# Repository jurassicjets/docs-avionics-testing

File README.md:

# Jurassic Jets — Avionics Documentation

Bench-test notes, pinout discoveries, signal traces, and "how does this LRU actually work" writeups for the electromechanical and early-digital avionics that lived in 707s, 727s, 737-classics, 747-classics, DC-8s, DC-9s, L-1011s, and their kin.

This repo is the institutional knowledge base for what we learn at the bench. It's organized so a contributor — sim enthusiast or active commercial captain — can find the unit they care about, see what's known about it, and add what they've learned.

## Navigation

The repo splits content along two axes: how the *airframe* is configured, and what each *unit* is.

- **[avionics/](avionics/)** — Unit-level registry. One folder per LRU type, documenting pinouts, behavior, bench tests, quirks, datasheets — written once regardless of how many copies exist or how many airframes carry it.
- **[aircraft/](aircraft/)** — Per-airframe configuration. Each aircraft has cockpit map and `panels/<panel>/<module>/` — the module README is the leaf and lists each install slot, linking out to `avionics/`. Currently: [b747-300-ja8179](aircraft/b747-300-ja8179/README.md).
- **[systems/](systems/)** — Cross-cutting topics that span multiple instruments and airframes: ARINC 429, synchros, 28 VDC distribution, 400 Hz AC, etc. Also where generic test methods (sniffing a bus, exciting a synchro) live, alongside the protocol they apply to.
- **[templates/](templates/)** — Starter scaffolds. Copy-paste, then fill in.
- **[glossary.md](glossary.md)** — Acronyms, part-number conventions, and term-of-art definitions.

## Contributing

Read **[CONTRIBUTING.md](CONTRIBUTING.md)** before adding content. It covers naming conventions, the per-instrument file skeleton, image and large-file handling, and how to handle instruments that appear in multiple aircraft.

## Docs site

Rendered with [MkDocs Material](https://squidfunk.github.io/mkdocs-material/) and deployed to **[avionics-docs.jurassicjets.com](https://avionics-docs.jurassicjets.com/)** on every push to `main` via [GitHub Actions](https://github.com/jurassicjets/docs-avionics-testing/blob/main/.github/workflows/docs.yml). GitHub also renders the markdown directly in this repo, so you don't need any tooling to read or contribute.

### Building the site locally

MkDocs forbids `docs_dir` from being the parent of `mkdocs.yml`, but we want content to live at the repo root rather than under a `docs/` wrapper. The build uses a tiny staging step ([`scripts/stage_docs.sh`](scripts/stage_docs.sh)) that creates a `_site_src/` directory of symlinks pointing back to the real files. Edits to the source files are visible immediately because they're symlinks, so `mkdocs serve` works normally after one stage.

```bash
pip install -r requirements-docs.txt
./scripts/stage_docs.sh
mkdocs serve
```

Then open <http://localhost:8000>. Edits to existing files hot-reload; if you add a new top-level item (a new directory at the repo root), re-run `./scripts/stage_docs.sh`.

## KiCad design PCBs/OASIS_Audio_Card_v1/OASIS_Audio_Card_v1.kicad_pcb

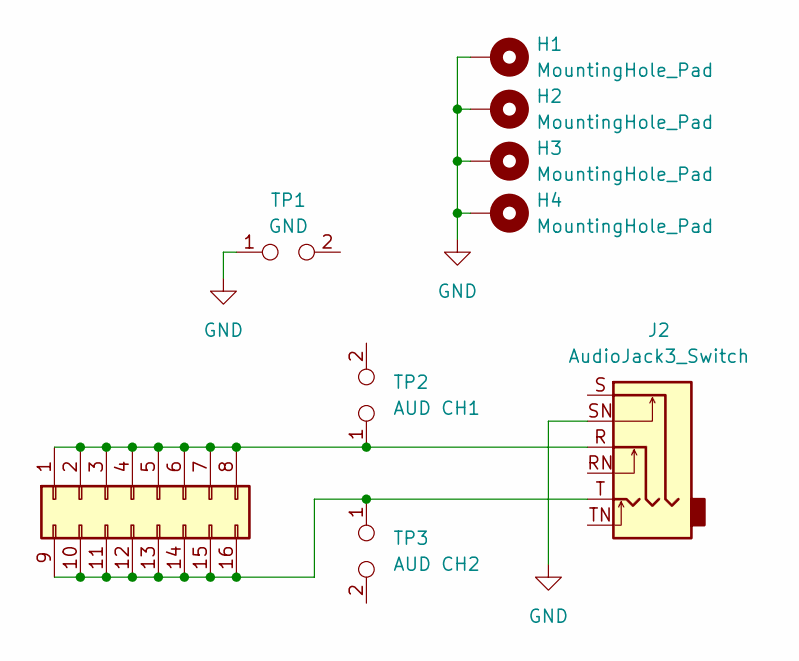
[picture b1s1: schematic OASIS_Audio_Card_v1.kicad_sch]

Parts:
H1, H2, H3, H4: MountingHole_Pad; MountingHole_3.2mm_M3_Pad
J1: Conn_02x08_Top_Bottom; 2x08_3.5mm_Phoenix_Connector_knockoff_convertible
J2: AudioJack3_Switch; TRS_2_Pole_THT
TP1: GND; PinHeader_1x02_P2.54mm_Vertical
TP2: AUD CH1; PinHeader_1x02_P2.54mm_Vertical
TP3: AUD CH2; PinHeader_1x02_P2.54mm_Vertical

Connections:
GND: H1.1, H2.1, H3.1, H4.1, J2.SN, TP1.1
unnamed: J1.1, J1.2, J1.3, J1.4, J1.5, J1.6, J1.7, J1.8, J2.R, TP2.1
unnamed: J1.9, J1.10, J1.11, J1.12, J1.13, J1.14, J1.15, J1.16, J2.T, TP3.1

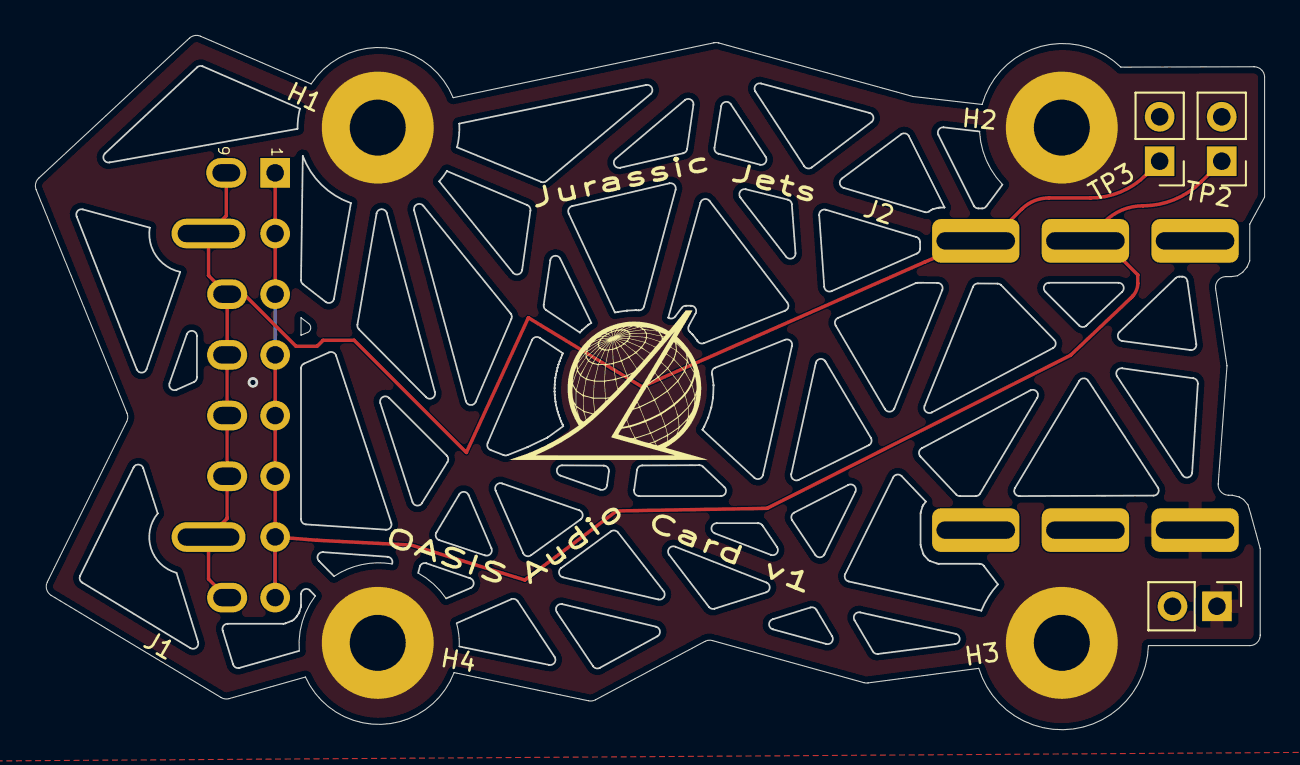
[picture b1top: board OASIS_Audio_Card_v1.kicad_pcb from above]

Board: 2 copper layers, 70.3 x 39.7 mm, 9 parts (0 on the bottom side), 3 nets.

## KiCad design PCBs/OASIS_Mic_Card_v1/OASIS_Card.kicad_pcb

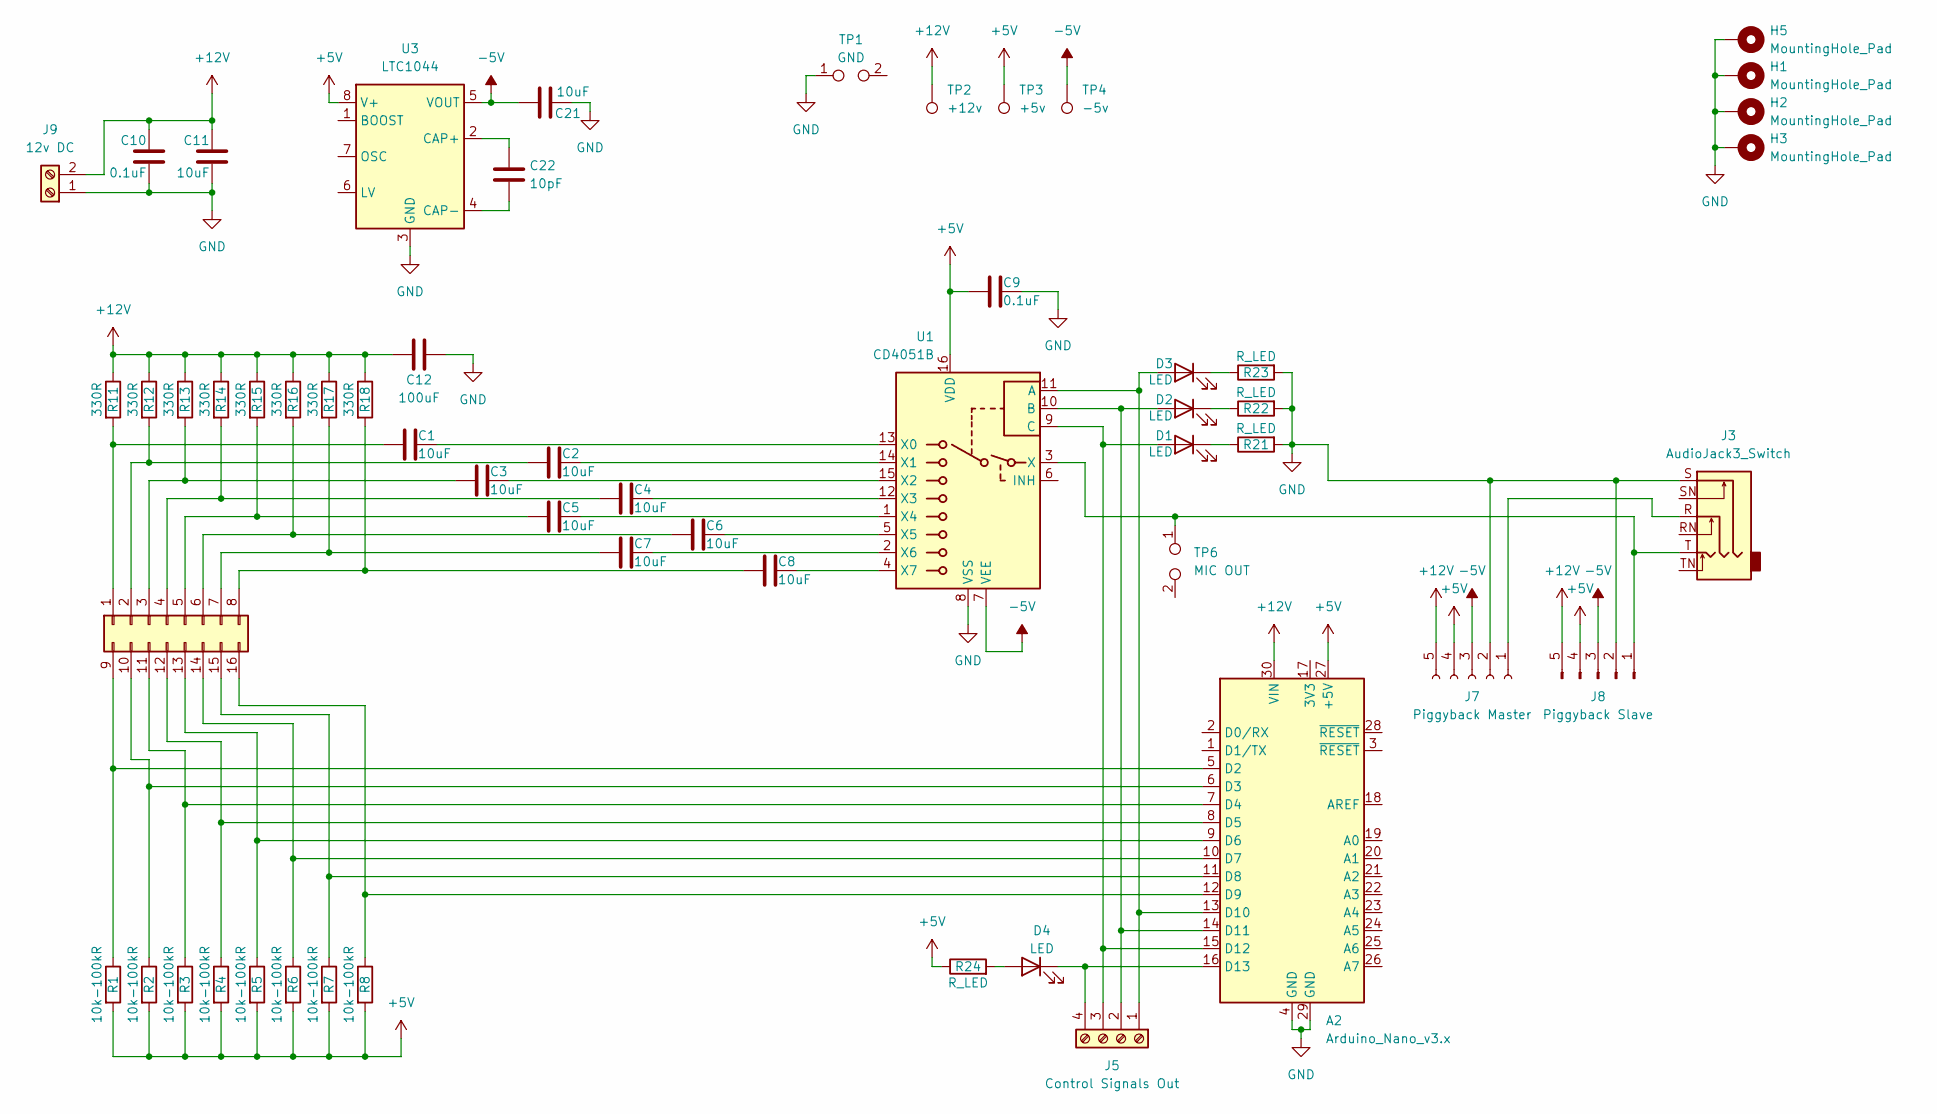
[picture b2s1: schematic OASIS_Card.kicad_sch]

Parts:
A2: Arduino_Nano_v3.x; Arduino_Nano
C1, C2, C3, C4, C5, C6, C7, C8, C11, C21: 10uF; C_1206_3216Metric_Pad1.33x1.80mm_HandSolder
C9, C10: 0.1uF; C_1206_3216Metric_Pad1.33x1.80mm_HandSolder
C12: 100uF; C_Radial_D6.3mm_H11.0mm_P2.50mm
C22: 10pF; C_1206_3216Metric_Pad1.33x1.80mm_HandSolder
D1, D2, D3, D4: LED; LED_0805_2012Metric
H1, H2, H3, H5: MountingHole_Pad; MountingHole_3.2mm_M3_Pad
J1: Conn_02x08_Top_Bottom; 2x08_3.5mm_Phoenix_Connector_knockoff
J3: AudioJack3_Switch; TRS_2_Pole_THT
J5: Control Signals Out; TerminalBlock_Phoenix_MKDS-1,5-4-5.08_1x04_P5.08mm_Horizont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
J7: Piggyback Master; PinHeader_1x05_P2.54mm_Vertical
J8: Piggyback Slave; PinHeader_1x05_P2.54mm_Vertical
J9: 12v DC; TerminalBlock_Phoenix_MKDS-1,5-2-5.08_1x02_P5.08mm_Horizont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
R1, R2, R3, R4, R5, R6, R7, R8: 10k-100kR; R_0805_2012Metric_Pad1.20x1.40mm_HandSolder
R11, R12, R13, R14, R15, R16, R17, R18: 330R; R_0805_2012Metric_Pad1.20x1.40mm_HandSolder
R21, R22, R23, R24: R_LED; R_0805_2012Metric_Pad1.20x1.40mm_HandSolder
TP1: GND; PinHeader_1x02_P2.54mm_Vertical
TP2: +12v; TestPoint_Pad_2.5x2.5mm
TP3: +5v; TestPoint_Pad_2.5x2.5mm
TP4: -5v; TestPoint_Pad_2.5x2.5mm
TP6: MIC OUT; PinHeader_1x02_P2.54mm_Vertical
U1: CD4051B; DIP-16_W7.62mm
U3: LTC1044; DIP-8_W7.62mm

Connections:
+5V: A2.27 (+5V), C9.1, J7.4, J8.4, R1.2, R2.2, R3.2, R4.2, R5.2, R6.2, R7.2, R8.2, R24.1, TP3.1, U1.16 (VDD), U3.8 (V+)
+12V: A2.30 (VIN), C10.2, C11.2, C12.2, J7.5, J8.5, J9.2, R11.1, R12.1, R13.1, R14.1, R15.1, R16.1, R17.1, R18.1, TP2.1
-5V: C21.2, J7.3, J8.3, TP4.1, U1.7 (VEE), U3.5 (VOUT)
GND: A2.4 (GND), A2.29 (GND), C9.2, C10.1, C11.1, C12.1, C21.1, H1.1, H2.1, H3.1, H5.1, J3.S, J7.2, J8.2, J9.1, R21.2, R22.2, R23.2, TP1.1, U1.8 (VSS), U3.3 (GND)
unnamed: A2.5 (D2), J1.9, R1.1
unnamed: A2.6 (D3), J1.10, R2.1
unnamed: A2.7 (D4), J1.11, R3.1
unnamed: A2.8 (D5), J1.12, R4.1
unnamed: A2.9 (D6), J1.13, R5.1
unnamed: A2.10 (D7), J1.14, R6.1
unnamed: A2.11 (D8), J1.15, R7.1
unnamed: A2.12 (D9), J1.16, R8.1
unnamed: A2.13 (D10), D3.2 (A), J5.1, U1.11 (A)
unnamed: A2.14 (D11), D2.2 (A), J5.2, U1.10 (B)
unnamed: A2.15 (D12), D1.2 (A), J5.3, U1.9 (C)
unnamed: A2.16 (D13), D4.1 (K), J5.4
unnamed: D1.1 (K), R21.1
unnamed: D2.1 (K), R22.1
unnamed: D3.1 (K), R23.1
unnamed: D4.2 (A), R24.2
unnamed: C1.1, J1.1, R11.2
unnamed: C2.1, J1.2, R12.2
unnamed: C3.1, J1.3, R13.2
unnamed: C4.1, J1.4, R14.2
unnamed: C5.1, J1.5, R15.2
unnamed: C6.1, J1.6, R16.2
unnamed: C7.1, J1.7, R17.2
unnamed: C8.1, J1.8, R18.2
unnamed: J3.R, J7.1
unnamed: J3.T, J8.1, TP6.1, U1.3 (X)
unnamed: C1.2, U1.13 (X0)
unnamed: C2.2, U1.14 (X1)
unnamed: C3.2, U1.15 (X2)
unnamed: C4.2, U1.12 (X3)
unnamed: C5.2, U1.1 (X4)
unnamed: C6.2, U1.5 (X5)
unnamed: C7.2, U1.2 (X6)
unnamed: C8.2, U1.4 (X7)
unnamed: C22.2, U3.2 (CAP+)
unnamed: C22.1, U3.4 (CAP-)

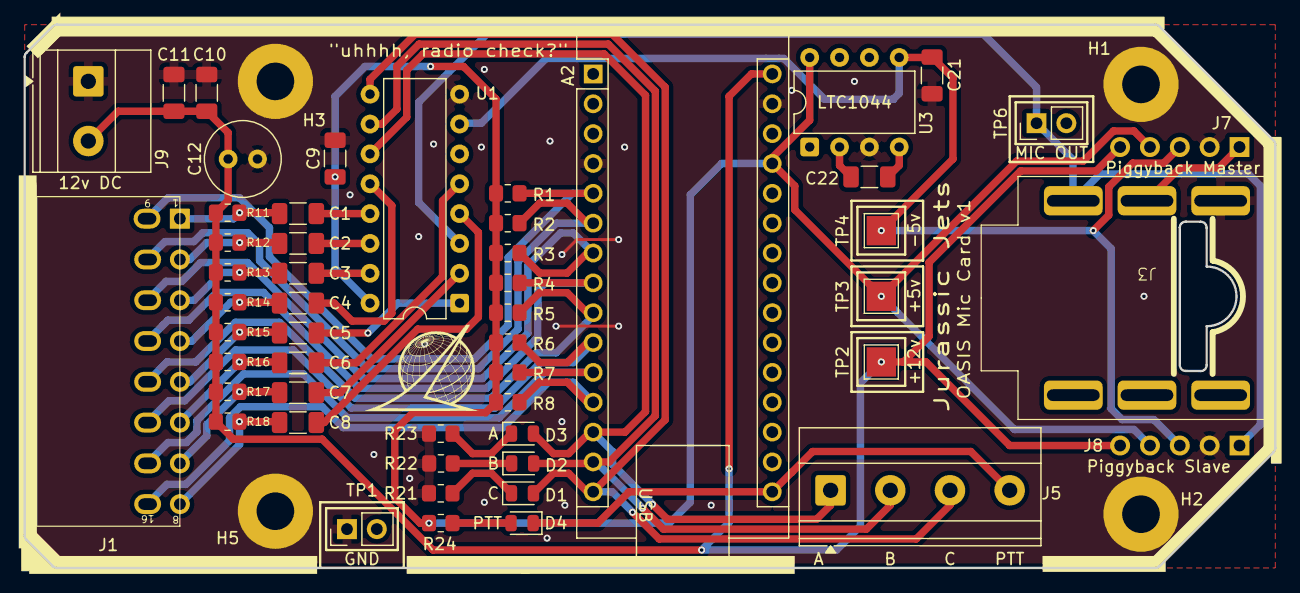
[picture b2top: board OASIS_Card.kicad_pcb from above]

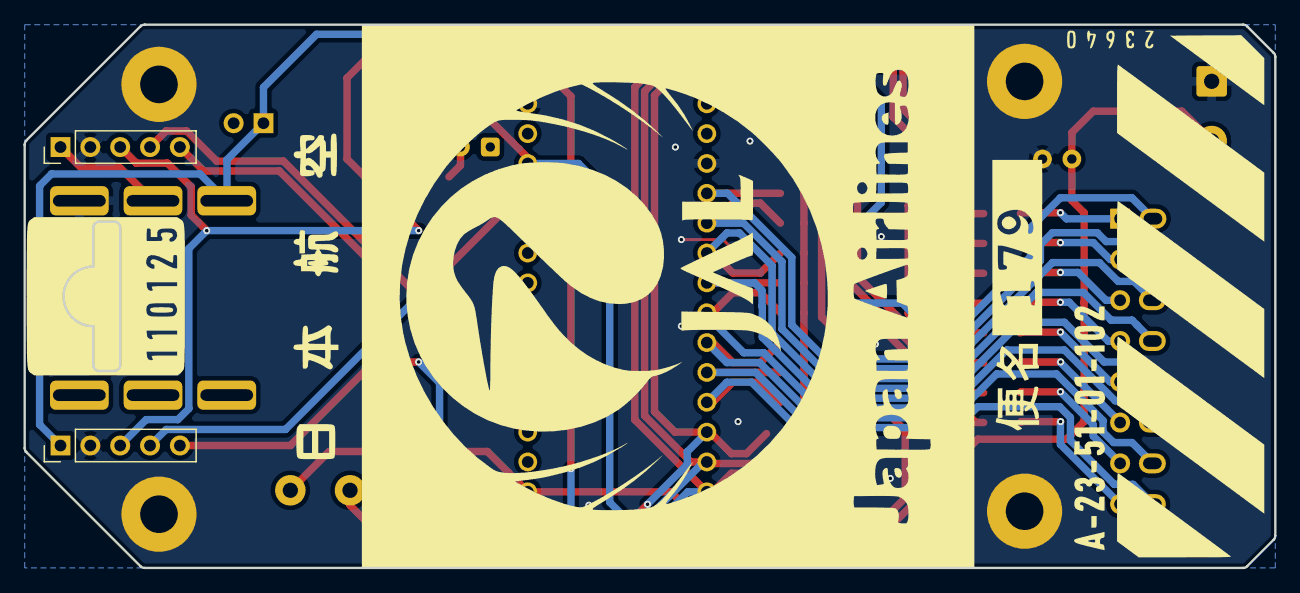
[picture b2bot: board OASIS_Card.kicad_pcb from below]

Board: 2 copper layers, 106.4 x 46.2 mm, 56 parts (2 on the bottom side), 40 nets.

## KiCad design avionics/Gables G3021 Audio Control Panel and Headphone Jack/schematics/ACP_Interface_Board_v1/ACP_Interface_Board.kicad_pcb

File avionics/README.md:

# Avionics

The unit-level registry. Every LRU we characterize gets one folder here, documenting its **intrinsic** properties — pinouts, signal behavior, bench-test observations, quirks, datasheets. The unit is documented once regardless of how many physical copies are installed or how many airframes carry it.

Aircraft panel/module docs describe *where* and *how* a unit is installed; this directory describes *what the unit is*. The two link to each other.

## Layout

```
avionics/<type>-<manufacturer>-<partnumber>/
├── README.md          identification, function, status, "installed in" links
├── pinouts.md         connector pinouts and signal definitions
├── bench-test.md      what we did, what we observed, with dates
├── photos/            pictures of instrument or test setup
├── captures/          scope traces, logic-analyzer dumps
├── schematics/        wiring diagrams, WDM pages, logic diagrams
└── datasheets/        manufacturer datasheets, AMM excerpts
```

See [`../CONTRIBUTING.md`](../CONTRIBUTING.md) for naming conventions, the file skeleton, and the slot-linking convention used in module READMEs.

## Index

_Add units here as they're documented. Group by function — the categories below are starters; add more as needed._

### Flight instruments
- _e.g._ `adi-collins-329b-8g` — Attitude Director Indicator

### Navigation
- _e.g._ `rmi-collins-331a-9g` — Radio Magnetic Indicator
- _e.g._ `civa-cdu-...` — CIVA INS Control Display Unit

### Communication

### Engine instruments

### Aircraft systems
- [`fqis-bfgoodrich-10106-03`](fqis-bfgoodrich-10106-03/README.md) — Fuel Quantity Indicator (747 center-wing-tank gauge)

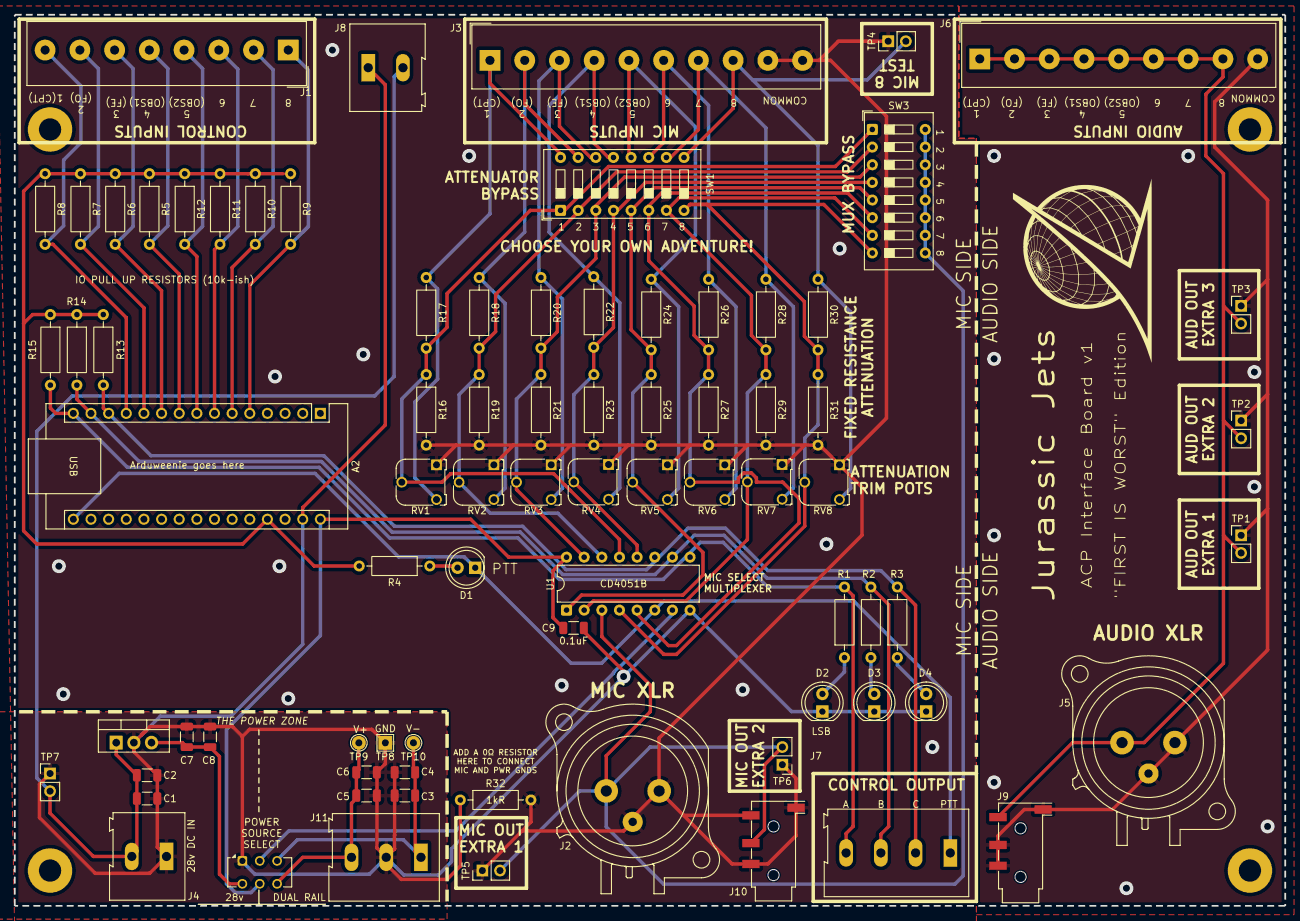
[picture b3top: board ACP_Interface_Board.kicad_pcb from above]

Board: 2 copper layers, 182.9 x 128.3 mm, 84 parts (0 on the bottom side), 44 nets.

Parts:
A2: Arduino_Nano_v3.x; Arduino_Nano
C1, C4, C6, C8: 10uF; C_1206_3216Metric
C2, C3, C5, C7, C9: 0.1uF; C_1206_3216Metric
D1, D2, D3, D4: Blue; LED_D5.0mm
H1, H2, H3, H4: MountingHole_Pad; MountingHole_3.2mm_M3_Pad
J1: Control Terminal Ship Side; Altech_AK100_1x08_P5.00mm
J2: Mic XLR; Jack_XLR_Neutrik_NC3FAAV-0_Vertical
J3: Mic Terminal Ship Side; Altech_AK100_1x10_P5.00mm
J4: 28v DC IN; TerminalBlock_Altech_AK300-2_P5.00mm
J5: Audio XLR; Jack_XLR_Neutrik_NC3FAAV-0_Vertical
J6: Audio Terminal Ship Side; Altech_AK100_1x09_P5.00mm
J7: Control Output; TerminalBlock_Altech_AK300-4_P5.00mm
J8: 28v DC OUT; TerminalBlock_Altech_AK300-2_P5.00mm
J9, J10: AudioPlug4; Jack_3.5mm_KoreanHropartsElec_PJ-320D-4A_Horizontal
J11: Dual Rail PWR IN; TerminalBlock_Altech_AK300-3_P5.00mm
R1, R2, R3, R4, R16, R17, R18, R19, R20, R21, R22, R23, R24, R25, R26, R27, R28, R29, R30, R31, R32: 1kR; R_Axial_DIN0207_L6.3mm_D2.5mm_P10.16mm_Horizontal
R5, R6, R7, R8, R9, R10, R11, R12, R13, R14, R15: 10kR; R_Axial_DIN0207_L6.3mm_D2.5mm_P10.16mm_Horizontal
RV1, RV2, RV3, RV4, RV5, RV6, RV7, RV8: 10R; Potentiometer_Runtron_RM-065_Vertical
SW1: Mic Attenuation Bypass; SW_DIP_SPSTx08_Slide_9.78x22.5mm_W7.62mm_P2.54mm
SW2: SW_Slide_DPDT; SW_CK_JS202011AQN_DPDT_Angled
SW3: Mic Mux Bypass; SW_DIP_SPSTx08_Slide_9.78x22.5mm_W7.62mm_P2.54mm
TP1, TP2, TP3, TP4, TP5, TP6, TP7: TestPoint_2Pole; PinHeader_1x02_P2.54mm_Vertical
TP8: GND; TestPoint_THTPad_2.0x2.0mm_Drill1.0mm
TP9: V+; TestPoint_THTPad_D2.0mm_Drill1.0mm
TP10: V-; TestPoint_THTPad_D2.0mm_Drill1.0mm
U1: CD4051B; DIP-16_W7.62mm
U2: L7812; TO-220-3_Vertical

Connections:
GND: A2.29 (GND), C1.2, C2.2, C3.2, C4.2, C5.1, C6.1, C7.2, C8.2, C9.2, D2.1 (K), D3.1 (K), D4.1 (K), J4.1, J8.1, J11.2, R32.1, SW2.1 (A), TP7.1, TP8.1, U1.8 (VSS), U2.2 (GND)
GND1: J2.1, J2.3, J3.9, J3.10, J10.R2, J10.S, J10.T, R16.2, R19.2, R21.2, R23.2, R25.2, R27.2, R29.2, R31.2, R32.2, RV1.1, RV2.1, RV3.1, RV4.1, RV5.1, RV6.1, RV7.1, RV8.1, TP4.1, TP5.1, TP6.1
GND2: J5.1, J5.3, J6.9, J9.R1, J9.R2, J9.S, TP1.1, TP2.1, TP3.1
unnamed: A2.27 (+5V), R4.2, R5.1, R6.1, R7.1, R8.1, R9.1, R10.1, R11.1, R12.1, R13.1, R14.1, R15.1
unnamed: A2.5 (D2), J1.1, R9.2
unnamed: A2.6 (D3), J1.2, R10.2
unnamed: A2.7 (D4), J1.3, R11.2
unnamed: A2.8 (D5), J1.4, R12.2
unnamed: A2.9 (D6), J1.5, R5.2
unnamed: A2.10 (D7), J1.6, R6.2
unnamed: A2.11 (D8), J1.7, R7.2
unnamed: A2.12 (D9), J1.8, R8.2
unnamed: A2.13 (D10), J7.2, R1.2, R13.2, U1.11 (A)
unnamed: A2.14 (D11), J7.3, R2.2, R14.2, U1.10 (B)
unnamed: A2.15 (D12), J7.4, R3.2, R15.2, U1.9 (C)
unnamed: A2.16 (D13), D1.1 (K), J7.1, U1.6 (INH)
unnamed: A2.30 (VIN), C9.1, SW2.5 (B), U1.16 (VDD)
unnamed: D1.2 (A), R4.1
unnamed: D2.2 (A), R3.1
unnamed: D3.2 (A), R2.1
unnamed: D4.2 (A), R1.1
unnamed: J3.1, R17.1, RV1.3, SW1.16
unnamed: J3.2, R18.1, RV2.3, SW1.15
unnamed: J3.3, R20.1, RV3.3, SW1.14
unnamed: J3.4, R22.1, RV4.3, SW1.13
unnamed: J3.5, R24.1, RV5.3, SW1.12
unnamed: J3.6, R26.1, RV6.3, SW1.11
unnamed: J3.7, R28.1, RV7.3, SW1.10
unnamed: J3.8, R30.1, RV8.3, SW1.9, TP4.2
unnamed: C1.1, C2.1, J4.2, J8.2, TP7.2, U2.1 (IN)
unnamed: J5.2, J6.1, J6.2, J6.3, J6.4, J6.5, J6.6, J6.7, J6.8, J9.T, TP1.2, TP2.2, TP3.2
unnamed: C3.1, C4.1, J11.1, SW2.3 (C), TP10.1
unnamed: C5.2, C6.2, J11.3, SW2.4 (A), TP9.1
unnamed: SW2.2 (B), U1.7 (VEE)
unnamed: R16.1, R17.2, RV1.2, SW1.1, SW3.1, U1.13 (X0)
unnamed: R18.2, R19.1, RV2.2, SW1.2, SW3.2, U1.14 (X1)
unnamed: R20.2, R21.1, RV3.2, SW1.3, SW3.3, U1.15 (X2)
unnamed: R22.2, R23.1, RV4.2, SW1.4, SW3.4, U1.12 (X3)
unnamed: R24.2, R25.1, RV5.2, SW1.5, SW3.5, U1.1 (X4)
unnamed: R26.2, R27.1, RV6.2, SW1.6, SW3.6, U1.5 (X5)
unnamed: R28.2, R29.1, RV7.2, SW1.7, SW3.7, U1.2 (X6)
unnamed: R30.2, R31.1, RV8.2, SW1.8, SW3.8, U1.4 (X7)
unnamed: J2.2, J10.R1, SW3.9, SW3.10, SW3.11, SW3.12, SW3.13, SW3.14, SW3.15, SW3.16, TP5.2, TP6.2, U1.3 (X)
unnamed: C7.1, C8.1, SW2.6 (C), U2.3 (OUT)

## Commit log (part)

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2026-05-04 tempalte updates
2026-05-04 tempalte updates, added CSD oil temp gauge (WIP)
2026-05-04 formatting
2026-05-17 fuel gauge ARINC testing
2026-05-21 added Kollsman VSI/RA
2026-05-24 fuel gauge stuff
2026-05-26 ACP and VHF radio
2026-05-27 ACP pinout
2026-05-27 OASIS schematic
2026-05-31 OASIS schematics
2026-06-02 audio boss
2026-06-02 audio boss tweaks
2026-06-04 a bunch of stuff
2026-06-05 audio demo
2026-06-06 audio boss source updates
2026-06-08 audio boss morse and file reading
2026-06-11 demo stuff
2026-06-16 OASIS card layout
2026-06-17 more OASIS card stuff
2026-06-24 lots of OASIS updates because I forgot to push for a while
2026-06-25 OASIS mic updates, audio layout madness
